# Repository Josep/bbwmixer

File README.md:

Audio Mixer and Volume MIDI controlled
======================================

This is a simple audio mixer with 4 analog stereo inputs and 1 output. The main volume 
and the volume of each input is controlled by MIDI messages.

The main volume is handled by the PGA2311 chip. The level of the 4 inputs are controlled by the
digital potentiometer MCP4251.

All the components are controlled by a Beaglebone White.

The midi interface is a classical one -not USB- with optocoupler 6N138.

The midi messages are handled in the PRU (Programmable Realtime Unit) of the Beaglebone.

No need to install capes or device tree overlays.

If you don't have a midi controller, the levels can be controlled from a web page too. In that case, an ethernet connection is needed.

Although the analog and digital power supply and grounds are separated in the design, they can be connected together with a jumper. So, the power from the BeagleBone will supply all the circuit. In my case, the results are good enough with the jumpers.

J1 pinout
---------

    1  Left CH1
    2  Left CH1 GND  
    3  Right CH1
    4  Right CH1 GND
    5  Left CH2 GND
    6  Left CH2
    7  Right CH2 GND
    8  Right CH2
    9  Left CH3
    10 Left CH3 GND
    11 Right CH3
    12 Right CH3 GND
    13 Left CH4 GND
    14 Left CH4
    15 Right CH4 GND
    16 Right CH4

J2 pinout
---------

    1  Left out
    2  Left out GND
    3  Right out
    4  Right out GND
    5  Midi in (optocoupler)
    6  NC
    7  Midi in (R220)
    8  NC
    9  NC
    10 NC
    11 +3.3V
    12 NC
    13 +5V Digital
    14 +5V Analog
    15 Digital GND
    16 Analog GND

Beaglebone pins used
--------------------

    P8_1   GND
    P8_2   GND
    P9_1   GND
    P9_2   GND
    P9_4   VDD_3V3
    P9_8   +5V
    P9_11  gpio0_30  MUTE PGA2311
    P9_12  gpio1_28  ZCEN PGA2311
    P9_13  gpio0_31  CS CH3 MCP4251
    P9_14  gpio1_18  CS CH4 MCP4251
    P9_15  gpio1_16  SHDN CH1 MCP4251
    P9_16  gpio1_19  CS CH2 MCP4251
    P9_17  gpio0_5   CS PGA2311
    P9_21  gpio0_3   SPI DATA OUT PGA2311
    P9_22  gpio0_2   SPI CLK PGA2311
    P9_23  gpio1_17  SHDN CH2 MCP4251
    P9_25  gpio3_21  SHDN CH3 MCP4251
    P9_27  gpio3_19  SHDN CH4 MCP4251
    P9_28  gpio3_17  CS CH1 MCP4251
    P9_29  gpio3_15  SPI DATA OUT MCP4251
    P9_30  gpio3_16  SPI DATA IN MCP4251
    P9_31  gpio3_14  SPI CLK MCP4251
    P9_42  gpio7_7   MIDI IN

MIDI Messages Handled
---------------------

    B0 44 7F  Mute ON Main Volume
    B0 44 00  Mute OFF Main Volume
    BA 46 7F  Mute ON CH1
    BA 46 00  Mute OFF CH1
    BA 47 7F  Mute ON CH2
    BA 47 00  Mute OFF CH2
    BA 48 7F  Mute ON CH3
    BA 48 00  Mute OFF CH3
    BA 49 7F  Mute ON CH4
    BA 49 00  Mute OFF CH4
    B0 07 XX  Main Volume (XX: 00-7F)
    BA 07 XX  CH1 Level (XX: 00-7F)
    BA 4A XX  CH2 Level (XX: 00-7F)
    BA 4B XX  CH3 Level (XX: 00-7F)
    BA 4C XX  CH4 Level (XX: 00-7F)

Versions
--------
    
    python3.7, tornado server 6.2

    debian@bbwmixer:/opt/scripts/tools$ sudo ./version.sh
    git:/opt/scripts/:[1b1122751f7051bd8996f353756ba6ff30e71820]
    eeprom:[A335BONE00A50812BB000078]
    model:[TI_AM335x_BeagleBone]
    dogtag:[BeagleBoard.org Debian Buster Console Image 2020-04-06]
    bootloader:[microSD-(push-button)]:[/dev/mmcblk0]:[U-Boot SPL 2019.04-00002-g07d5700e21 (Mar 06 2020 - 11:24:55 -0600)]:[location: dd MBR]
    bootloader:[microSD-(push-button)]:[/dev/mmcblk0]:[U-Boot 2019.04-00002-g07d5700e21]:[location: dd MBR]
    UBOOT: Booted Device-Tree:[am335x-bone-uboot-univ.dts]
    UBOOT: Loaded Overlay:[AM335X-PRU-RPROC-4-19-TI-00A0]
    kernel:[4.19.94-ti-r73]
    nodejs:[v10.24.0]
    /boot/uEnv.txt Settings:
    uboot_overlay_options:[enable_uboot_overlays=1]
    uboot_overlay_options:[disable_uboot_overlay_emmc=1]
    uboot_overlay_options:[disable_uboot_overlay_video=1]
    uboot_overlay_options:[disable_uboot_overlay_audio=1]
    uboot_overlay_options:[disable_uboot_overlay_wireless=1]
    uboot_overlay_options:[disable_uboot_overlay_adc=1]
    uboot_overlay_options:[uboot_overlay_pru=/lib/firmware/AM335X-PRU-RPROC-4-19-TI-00A0.dtbo]
    uboot_overlay_options:[enable_uboot_cape_universal=1]

Known issues
------------

- Hardware: The channels 3 and 4 SPI return information from the MCP4251 chip are not connected. A wire can be soldered if the SPI return information is needed. This is optional because the returned information is not used currently by the software.
- Software: The state of the mute buttons is not updated when the mixer is started. 
- Software: The response to the volume changes may be a little slow. This is due -I suppose- to the fact that the SPI protocol is implemented with GPIOs instead of the true SPI hardware included in the beaglebone. I tried but could not make it work.

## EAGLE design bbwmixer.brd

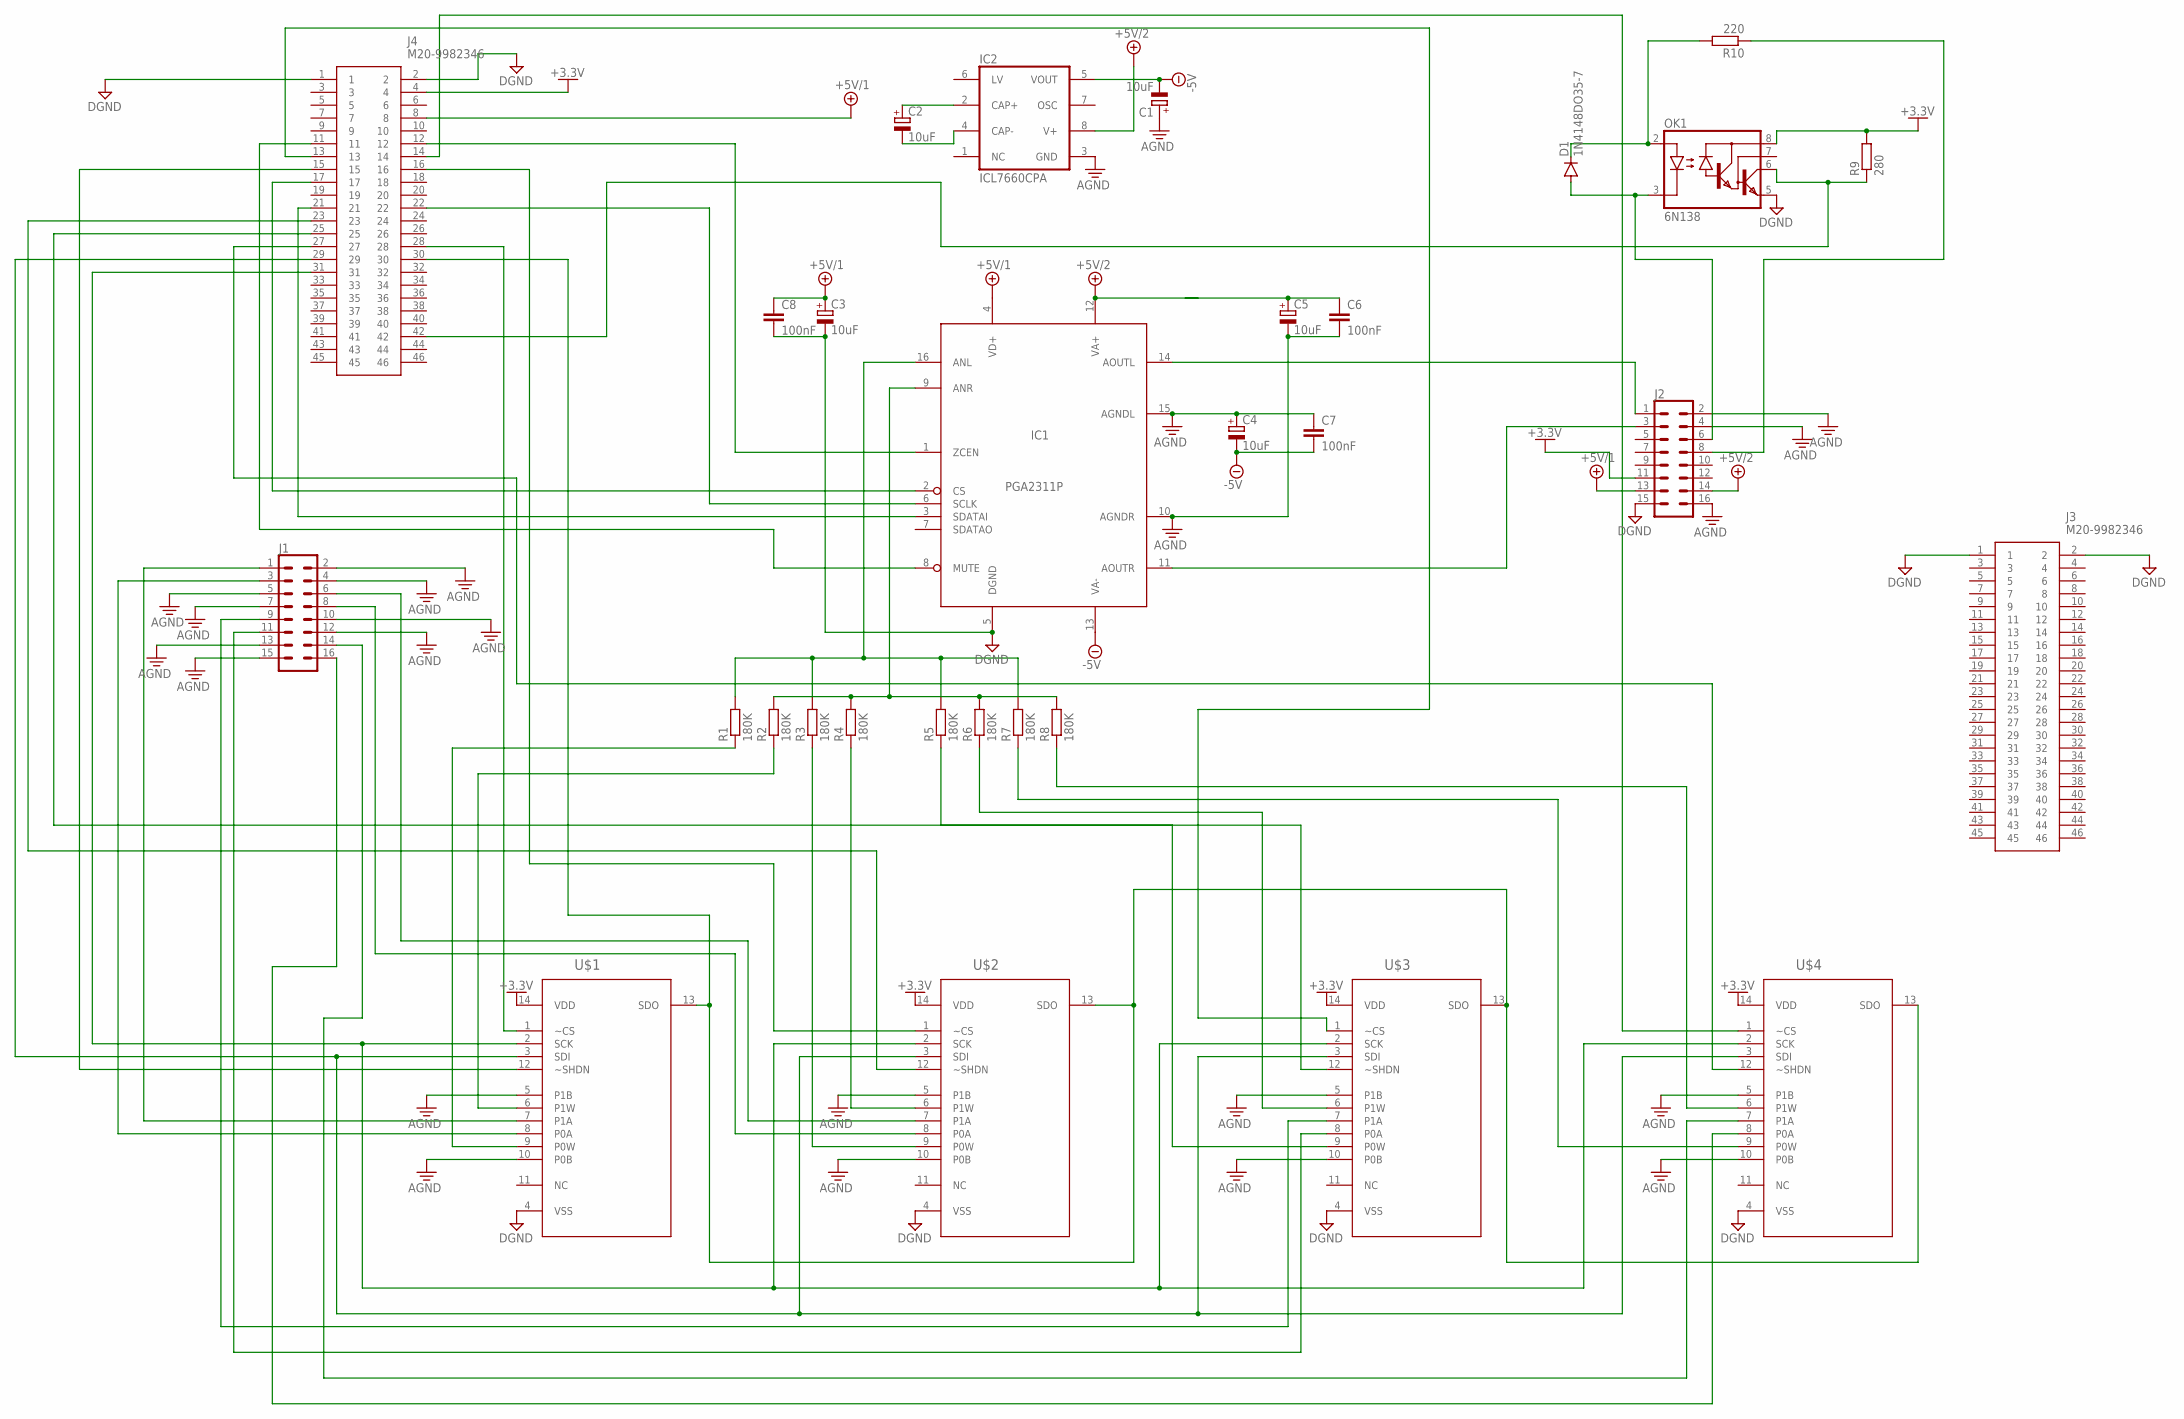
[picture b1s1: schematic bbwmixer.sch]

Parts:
C1, C2, C3, C4, C5: 10uF; E15-5
C6, C7, C8: 100nF; C050-025X075
D1: 1N4148DO35-7; DO35-7
IC1: PGA2311P; DIL16
IC2: ICL7660CPA; DIL08
J1, J2: CONN_08X2; 2X8
J3, J4: M20-9982346
OK1: 6N138; DIL08
R1, R2, R3, R4, R5, R6, R7, R8: 180K; 0207/10
R9: 280; 0207/10
R10: 220; 0207/10
U$1, U$2, U$3, U$4: MCP4251-103E/P; DIP254P762X533-14

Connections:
+3.3V: J2.11, J4.4, OK1.8 (VCC), R9.2, U$1.14 (VDD), U$2.14 (VDD), U$3.14 (VDD), U$4.14 (VDD)
+5V/1: C3.+, C8.1, IC1.4 (VD+), J2.13, J4.8
+5V/2: IC1.12 (VA+), IC2.8 (V+), J2.14
-5V: C1.-, C4.-, C7.2, IC1.13 (VA-), IC2.5 (VOUT)
AGND: C1.+, C4.+, C5.-, C6.2, C7.1, IC1.10 (AGNDR), IC1.15 (AGNDL), IC2.3 (GND), J1.2, J1.4, J1.5, J1.7, J1.10, J1.12, J1.13, J1.15, J2.2, J2.4, J2.16, U$1.5 (P1B), U$1.10 (P0B), U$2.5 (P1B), U$2.10 (P0B), U$3.5 (P1B), U$3.10 (P0B), U$4.5 (P1B), U$4.10 (P0B)
DGND: C3.-, C8.2, IC1.5 (DGND), J2.15, J3.1, J3.2, J4.1, J4.2, OK1.5 (GND), U$1.4 (VSS), U$2.4 (VSS), U$3.4 (VSS), U$4.4 (VSS)
unnamed: C2.+, IC2.2 (CAP+)
unnamed: C2.-, IC2.4 (CAP-)
unnamed: C5.+, C6.1
unnamed: R1.1, U$1.9 (P0W)
unnamed: R2.1, U$1.6 (P1W)
unnamed: R3.1, U$2.9 (P0W)
unnamed: R4.1, U$2.6 (P1W)
unnamed: R5.1, U$3.9 (P0W)
unnamed: R6.1, U$3.6 (P1W)
unnamed: R7.1, U$4.9 (P0W)
unnamed: R8.1, U$4.6 (P1W)
unnamed: IC1.16 (ANL), R1.2, R3.2, R5.2, R7.2
unnamed: IC1.9 (ANR), R2.2, R4.2, R6.2, R8.2
unnamed: J4.31, U$1.2 (SCK), U$2.2 (SCK), U$3.2 (SCK), U$4.2 (SCK)
unnamed: J1.3, U$1.8 (P0A)
unnamed: J4.29, U$1.3 (SDI), U$2.3 (SDI), U$3.3 (SDI), U$4.3 (SDI)
unnamed: J1.1, U$1.7 (P1A)
unnamed: J1.8, U$2.8 (P0A)
unnamed: J1.6, U$2.7 (P1A)
unnamed: J1.9, U$3.7 (P1A)
unnamed: J1.11, U$3.8 (P0A)
unnamed: J1.14, U$4.7 (P1A)
unnamed: J1.16, U$4.8 (P0A)
unnamed: IC1.14 (AOUTL), J2.1
unnamed: IC1.11 (AOUTR), J2.3
unnamed: IC1.2 (CS), J4.17
unnamed: IC1.3 (SDATAI), J4.21
unnamed: IC1.6 (SCLK), J4.22
unnamed: IC1.8 (MUTE), J4.11
unnamed: IC1.1 (ZCEN), J4.12
unnamed: J4.15, U$1.12 (~SHDN)
unnamed: J4.23, U$2.12 (~SHDN)
unnamed: J4.25, U$3.12 (~SHDN)
unnamed: J4.27, U$4.12 (~SHDN)
unnamed: J4.28, U$1.1 (~CS)
unnamed: J4.16, U$2.1 (~CS)
unnamed: J4.13, U$3.1 (~CS)
unnamed: J4.14, U$4.1 (~CS)
unnamed: J4.42, OK1.6 (VO), R9.1
unnamed: D1.A, J2.6, OK1.3 (C)
unnamed: D1.C, OK1.2 (A), R10.2
unnamed: J2.8, R10.1

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
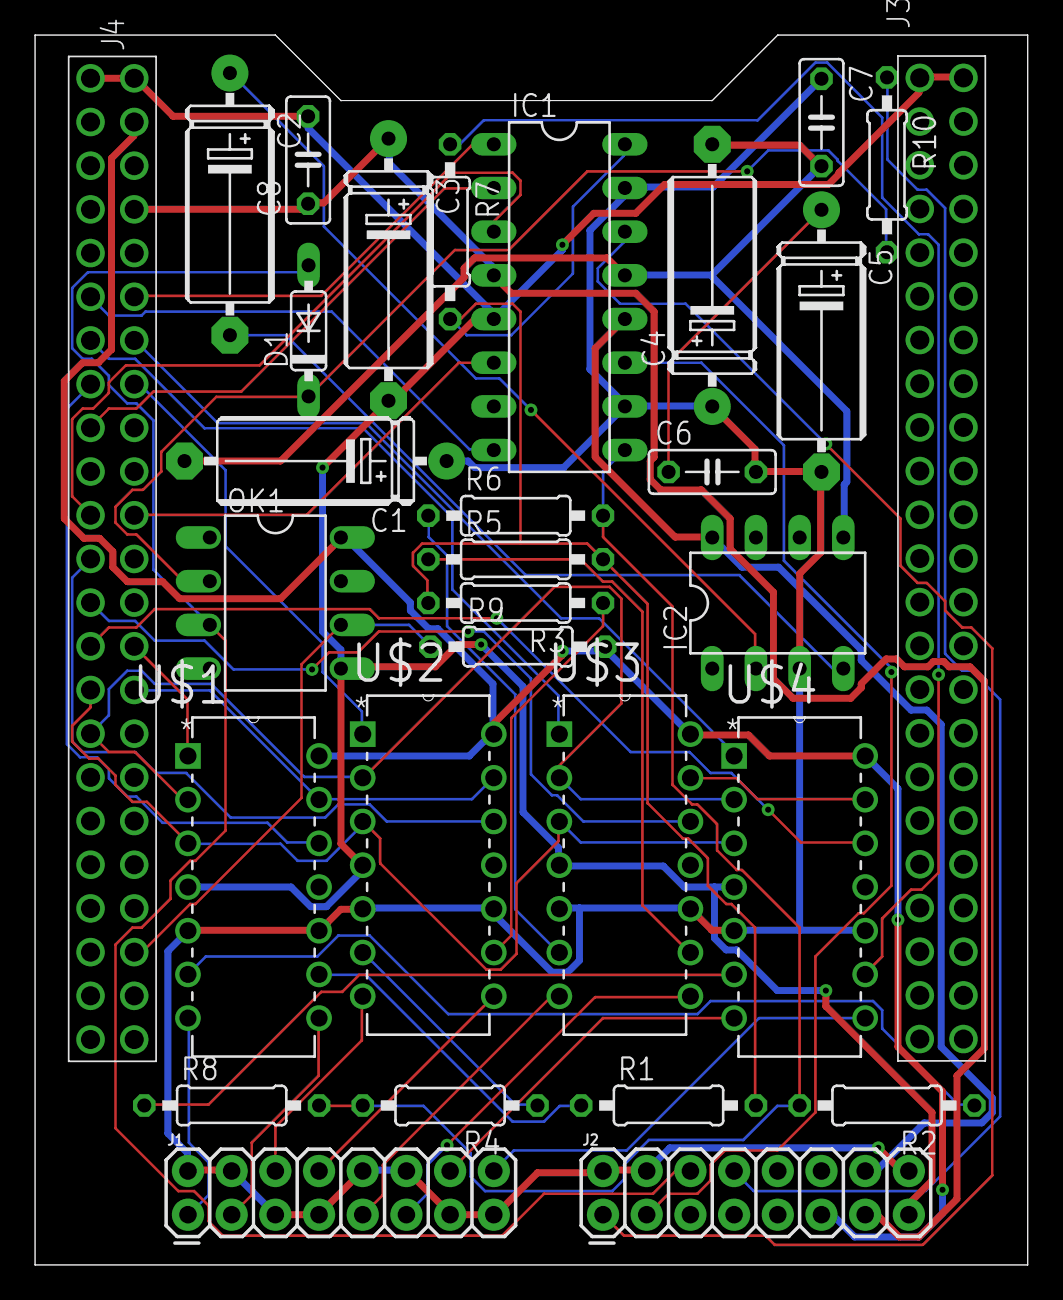
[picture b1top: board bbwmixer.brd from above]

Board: 2 copper layers, 57.7 x 71.5 mm, 30 parts (0 on the bottom side), 50 nets.

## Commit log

2023-05-18 inital release
2023-05-24 schematic and pcb

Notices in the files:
parts and their libraries:
SparkFun-Connectors: Licensing: Creative Commons ShareAlike 4.0 International - https://creativecommons.org/licenses/by-sa/4.0
